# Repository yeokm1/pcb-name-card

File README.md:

# pcb-name-card

My name or business card that is on a Printed Circuit Board (PCB). Comes with an white LED, UV LED and a ruler. Not forgetting a QR code containing my contact details in [Vcard](https://en.wikipedia.org/wiki/VCard) format.

The lastest iteration of my name card is now in white.

I gave a talk on my name card, slides available in the picture link below.

###PCB Design software and addons/references used

1. Eagle 7.3.0: I use Standard but Light should still be able to open/modify the files.
2. Modified CR2032 library based on [here](https://github.com/nickaknudson/eagle-nickaknudson/blob/master/cr2032.lbr)
2. Elecrow Design Rule Check for 2 layers (in repo as `Elecrow_2-layer_eagle_rule.dru`)
3. Elecrow Gerber Generater 2-layer board (in repo as `Elecrow_Gerber_Generater_DrillAlign.cam`)
4. QR code generated from [here](http://goqr.me/)

###Schematic drawings

Images are exported from Eagle at 600dpi.

The board layout as seen in Eagle.

The board schematic as seen in Eagle.

###Bill of Materials (BOM) for components only

Components in their raw form

Components still in their original packets from different suppliers.

Assume minimum order 10 pieces, cost in Singapore dollars. There are additional savings if I order more say 50 units but the savings are still small. Delivery for BOM not included.

The BOM is available in the odt spreadsheets in this repo.

###PCB fabrication

PCB fabrication is currently done by [Elecrow (10-pieces-link)](http://www.elecrow.com/10pcs-2-layer-pcb-p-1175.html) or [(50-pieces-link)](http://www.elecrow.com/50pcs-2-layer-pcb-enig-p-1172.html) based on the following settings. Remember to consult the order submission specifications at the bottom of the previous link before submitting. Use the provided Gerber generator to produce the Gerber files.

####My Fabrication Settings:

1. Layer: 2
2. PCB Thickness: 0.6mm
3. Copper Weight : 1oz 35um (NA for 50 pieces)
4. PCB Size : 10cm Max * 10cm Max (or 50cm2 for 50 pieces)
5. PCB Color : Blue or Black
6. Surface Finish: ENIG
7. PCB Stencil : NO Stencil
8. Lead time : Shipped in 4 to 7 days (NA for 50 pieces)
9. Panelizing : Single PCB with milling

###PCB Cost including delivery
Assume US$1 = SG$1.3

####Unit cost for 10 PCBs only
Total PCB Cost: US$30.80 + US$16.17 (DHL) = US$46.97  
Individual PCB Cost: (US$46.97 * 1.3) / 10 = SG$6.10  

####Unit cost for 50 PCBs only
Total PCB Cost: US$62.47 + US$18.81 (DHL) = US$81.28  
Individual PCB Cost: (US$81.28 * 1.3) / 50 = SG$2.11  

###Total Unit cost (SGD$) with components

| Pieces | Young Blue | Formal Black |
|--------|------------|--------------|
| 10 | $15.53 | $17.19 |
| 50 | $10.53 | $12.26 |

#References
1. [How to design a 13.56 MHz
customized tag antenna](http://www.st.com/st-web-ui/static/active/jp/resource/technical/document/application_note/CD00221490.pdf)
2. [The impact of high pulse drain on CR2032 coin-cell battery capacity](http://m.eet.com/media/1121454/c0924post.pdf)
3. [Panasonic NFC Design Navigator](http://www.semicon.panasonic.co.jp/en/tool/nfcdesignnavigator/)

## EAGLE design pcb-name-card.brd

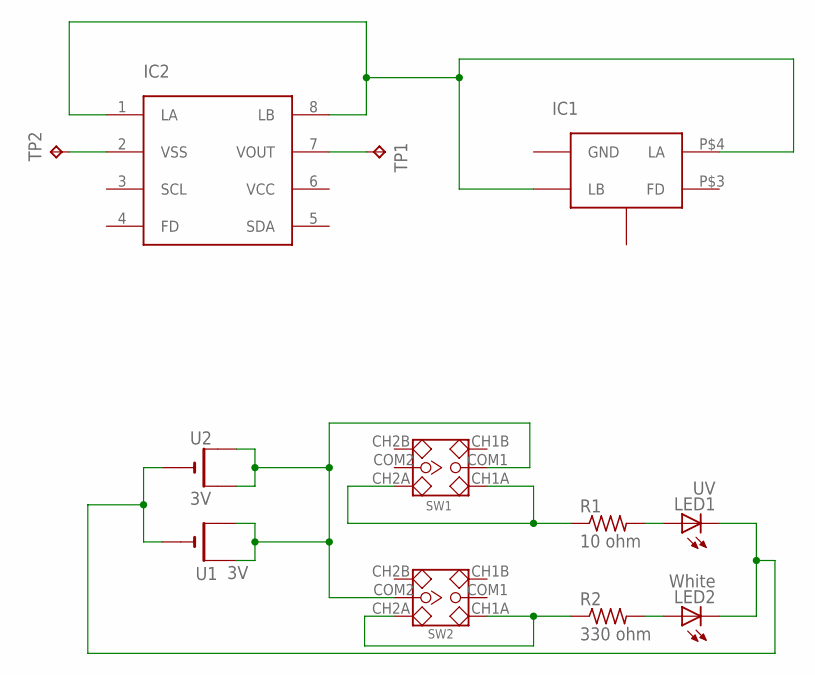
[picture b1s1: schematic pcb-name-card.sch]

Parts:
IC1: NTAG21XFDRC-FIT; HXSON4-SMALL
IC2: NT3H1X01W0FTT; TSSOP-8
LED1: UV; PLCC2
LED2: White; PLCC2
R1: 10 ohm; R2010
R2: 330 ohm; R2010
SW1, SW2: SMD-TOGGLE-SWITCH-2CH(2X3P-7X3.5MM); SW6-2.54-SMD-7.0X3.5X1.5MM
TP1: VOUT; B2,54
TP2: GND; B2,54
U1, U2: 3V; CR2032-SMD

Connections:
unnamed: LED1.A, R1.2
unnamed: LED2.A, R2.2
unnamed: R1.1, SW1.CH1A, SW1.CH2A
unnamed: R2.1, SW2.CH1A, SW2.CH2A
unnamed: IC1.P$2 (LB), IC1.P$4 (LA), IC2.1 (LA), IC2.8 (LB)
unnamed: LED1.C, LED2.C, U1.-, U2.-
unnamed: SW1.COM1, SW2.COM2, U1.+$1 (+), U1.+$2 (+1), U2.+$1 (+), U2.+$2 (+1)
unnamed: IC2.2 (VSS), TP2.TP
unnamed: IC2.7 (VOUT), TP1.TP

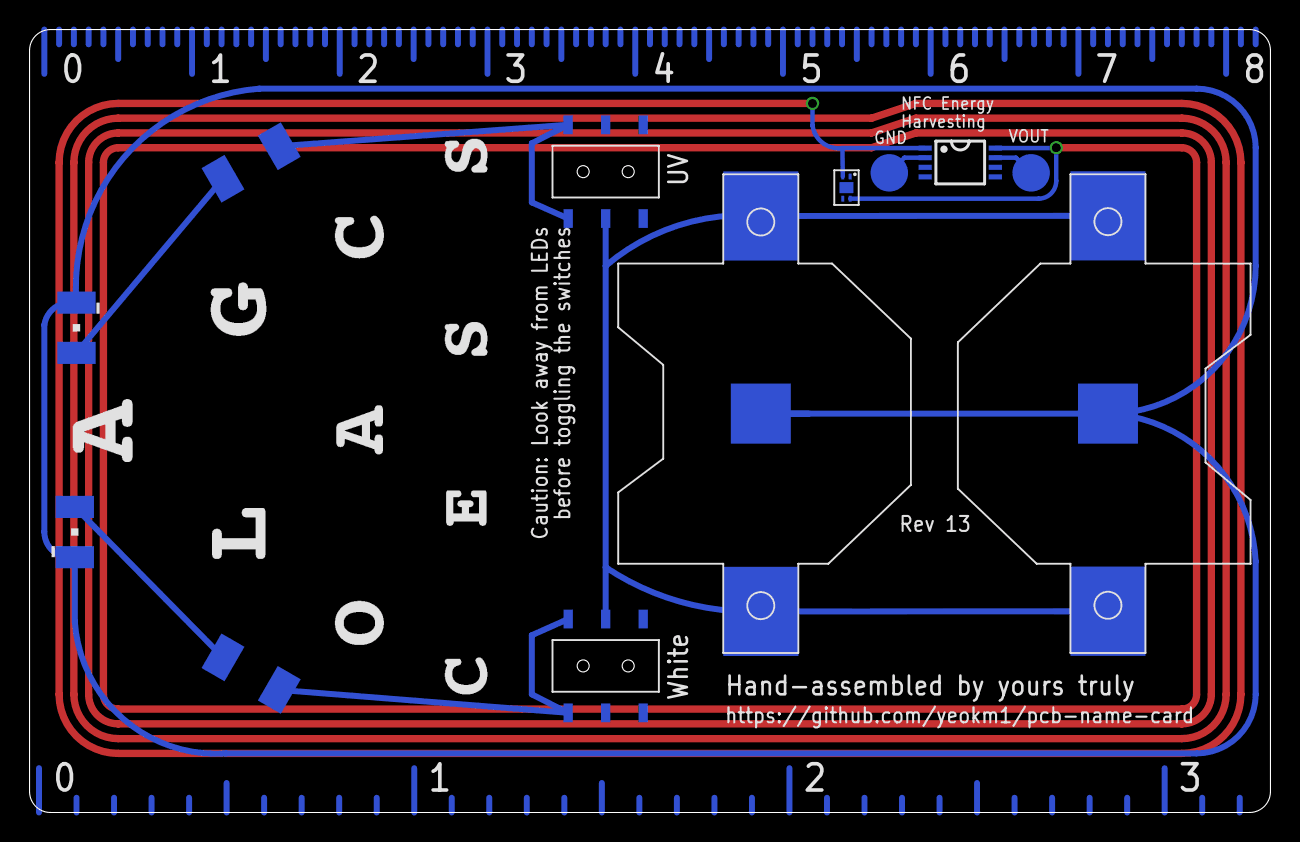
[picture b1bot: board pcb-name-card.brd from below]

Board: 2 copper layers, 84.0 x 53.0 mm, 12 parts (12 on the bottom side), 9 nets.

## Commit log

2015-06-28 aa banner
2015-06-28 more changes
2015-06-28 some changes
2015-06-28 some updates
2015-06-28 dimension
2015-06-28 reimport qr code
2015-06-28 qr code
2015-06-28 all items in
2015-06-28 cm ruler
2015-06-28 inch ruler
2015-06-28 add personal website in text
2015-06-28 qr code message
2015-06-28 new qr images
2015-06-28 qr inversion
2015-06-28 new qr code image
2015-06-28 + - signs around led
2015-06-28 revision 2 begins
2015-06-28 rev 2
2015-06-29 remove name of qr code
2015-07-28 vector font
2015-07-28 remove labels
2015-07-28 extra wiring
2015-07-28 miter edges
2015-07-28 alignment
2015-07-28 hand assembly text
2015-07-28 hand assembled by yours truly
2015-07-28 alignment issues
2015-07-29 change label position
2015-07-29 view all
2015-08-04 rev 3. one line on top layer so PCB manufacturers don't give me issue about missing top layer
2015-08-05 larger positive battery contacts
2015-08-05 battery position
2015-08-05 see top layer
2015-08-05 make trace straighter
2015-08-05 elecrow files
2015-08-18 remove battery text
2015-08-18 some text changes
2015-08-18 shift some stuff forward by 1mm
2015-08-18 top square around QR code
2015-08-18 make square around qr code larger
2015-08-24 rev 5 switch position
2015-08-29 remove seeed dru
2015-08-29 reduce size of schematic
2015-08-29 board images
2015-08-29 move to folder
2015-08-29 shift white led abit
2015-08-29 mitre edges further
2015-08-29 shift files in
2015-08-29 rev 6 board.png
2015-08-29 add extra redundant wire for ground
2015-08-29 image
2015-08-29 qr code to vcard
2015-08-29 change qr code
2015-08-29 details shift down
2015-08-29 change phone number to +65
2015-08-30 adjusted redundant ground wire around led
2015-08-31 change developer to engineer
2015-08-31 board png
2015-09-11 shift bottom text
2015-09-11 shift battery a little back
2015-09-11 up to rev 7
2015-09-11 new rev 7 board image
2015-09-11 images
2015-09-14 add missing 3 inch marking
2015-09-14 board.png
2015-10-03 update to rev 7 pcb images
2015-10-03 update text to reflect Rev 7
2015-10-03 spacing issue
2015-12-11 move to standard folders
2015-12-11 bom in spreadsheet
2015-12-11 remove old BOM file
2016-01-15 adjust formatting
2016-01-26 ntag21xf lbr
2016-01-26 support nfc band
2016-01-26 reference design from panasonic nfc design navigator http://www.semicon.panasonic.co.jp/en/tool/nfcdesignnavigator/
2016-01-27 shift warning text back up
2016-01-27 rev8 pcb with ntag216
2016-01-27 use ntag i2c
2016-01-27 nfc logo
2016-01-27 adjusted ruler labels
2016-01-27 rev 9 gerbel
2016-01-27 redundant ground wire
2016-01-27 view layer
2016-01-27 new rev 9 gerbel
2016-02-03 adjust S silkscreen pos
2016-02-03 nt35 data sheet
2016-02-04 adjusted size of ntag i2c
2016-02-04 combine both tag footprints on design
2016-02-04 adjust ntag21xf lbr to make pin 1 dot bigger
2016-02-04 add curvature to NFC wires
2016-02-12 NFC harvesting test points
2016-02-12 simpler ntag datasheets
2016-02-12 rev 10 gerber
2016-02-12 rename gerber directory
2016-02-13 update BOM with NFC chips
2016-02-13 consolidate short qr code folder
2016-02-13 extended vcard and qr
2016-02-27 presentation details
2016-03-07 adjusted silkscreen and some wiring pos
2016-03-07 qr code uses extended version and assumes black silkscreen on white soldermask
2016-03-08 rev 11
2016-03-14 adjusted font thickness and silkscreen positions
2016-03-14 some adjustments
2016-03-14 rev12 gerber
2016-03-16 update images to rev 12
2016-03-25 increase font ratio to 14%
2016-03-25 update to rev 13
2016-07-05 newer pcb name card image
